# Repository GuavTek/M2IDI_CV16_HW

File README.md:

This eurorack module has 16 general purpose outputs which can be used for: CV, gates, envelopes, LFOs+++. 
View this project on [CADLAB.io](https://cadlab.io/project/25235) to see renders of schematics and PCBs, as well as current issues. 

<h2> A part of the M2IDI prototypes </h2>

<p>
The code for this module can be found on  
<a href="https://github.com/GuavTek/M2IDI_CV16">
			  GitHub
		  </a>
</p>

<p> 
More info on the M2IDI system can be found on the 
<a href="https://hackaday.io/project/182092-modular-midi">
			  Hackaday project page
		  </a>

</p>

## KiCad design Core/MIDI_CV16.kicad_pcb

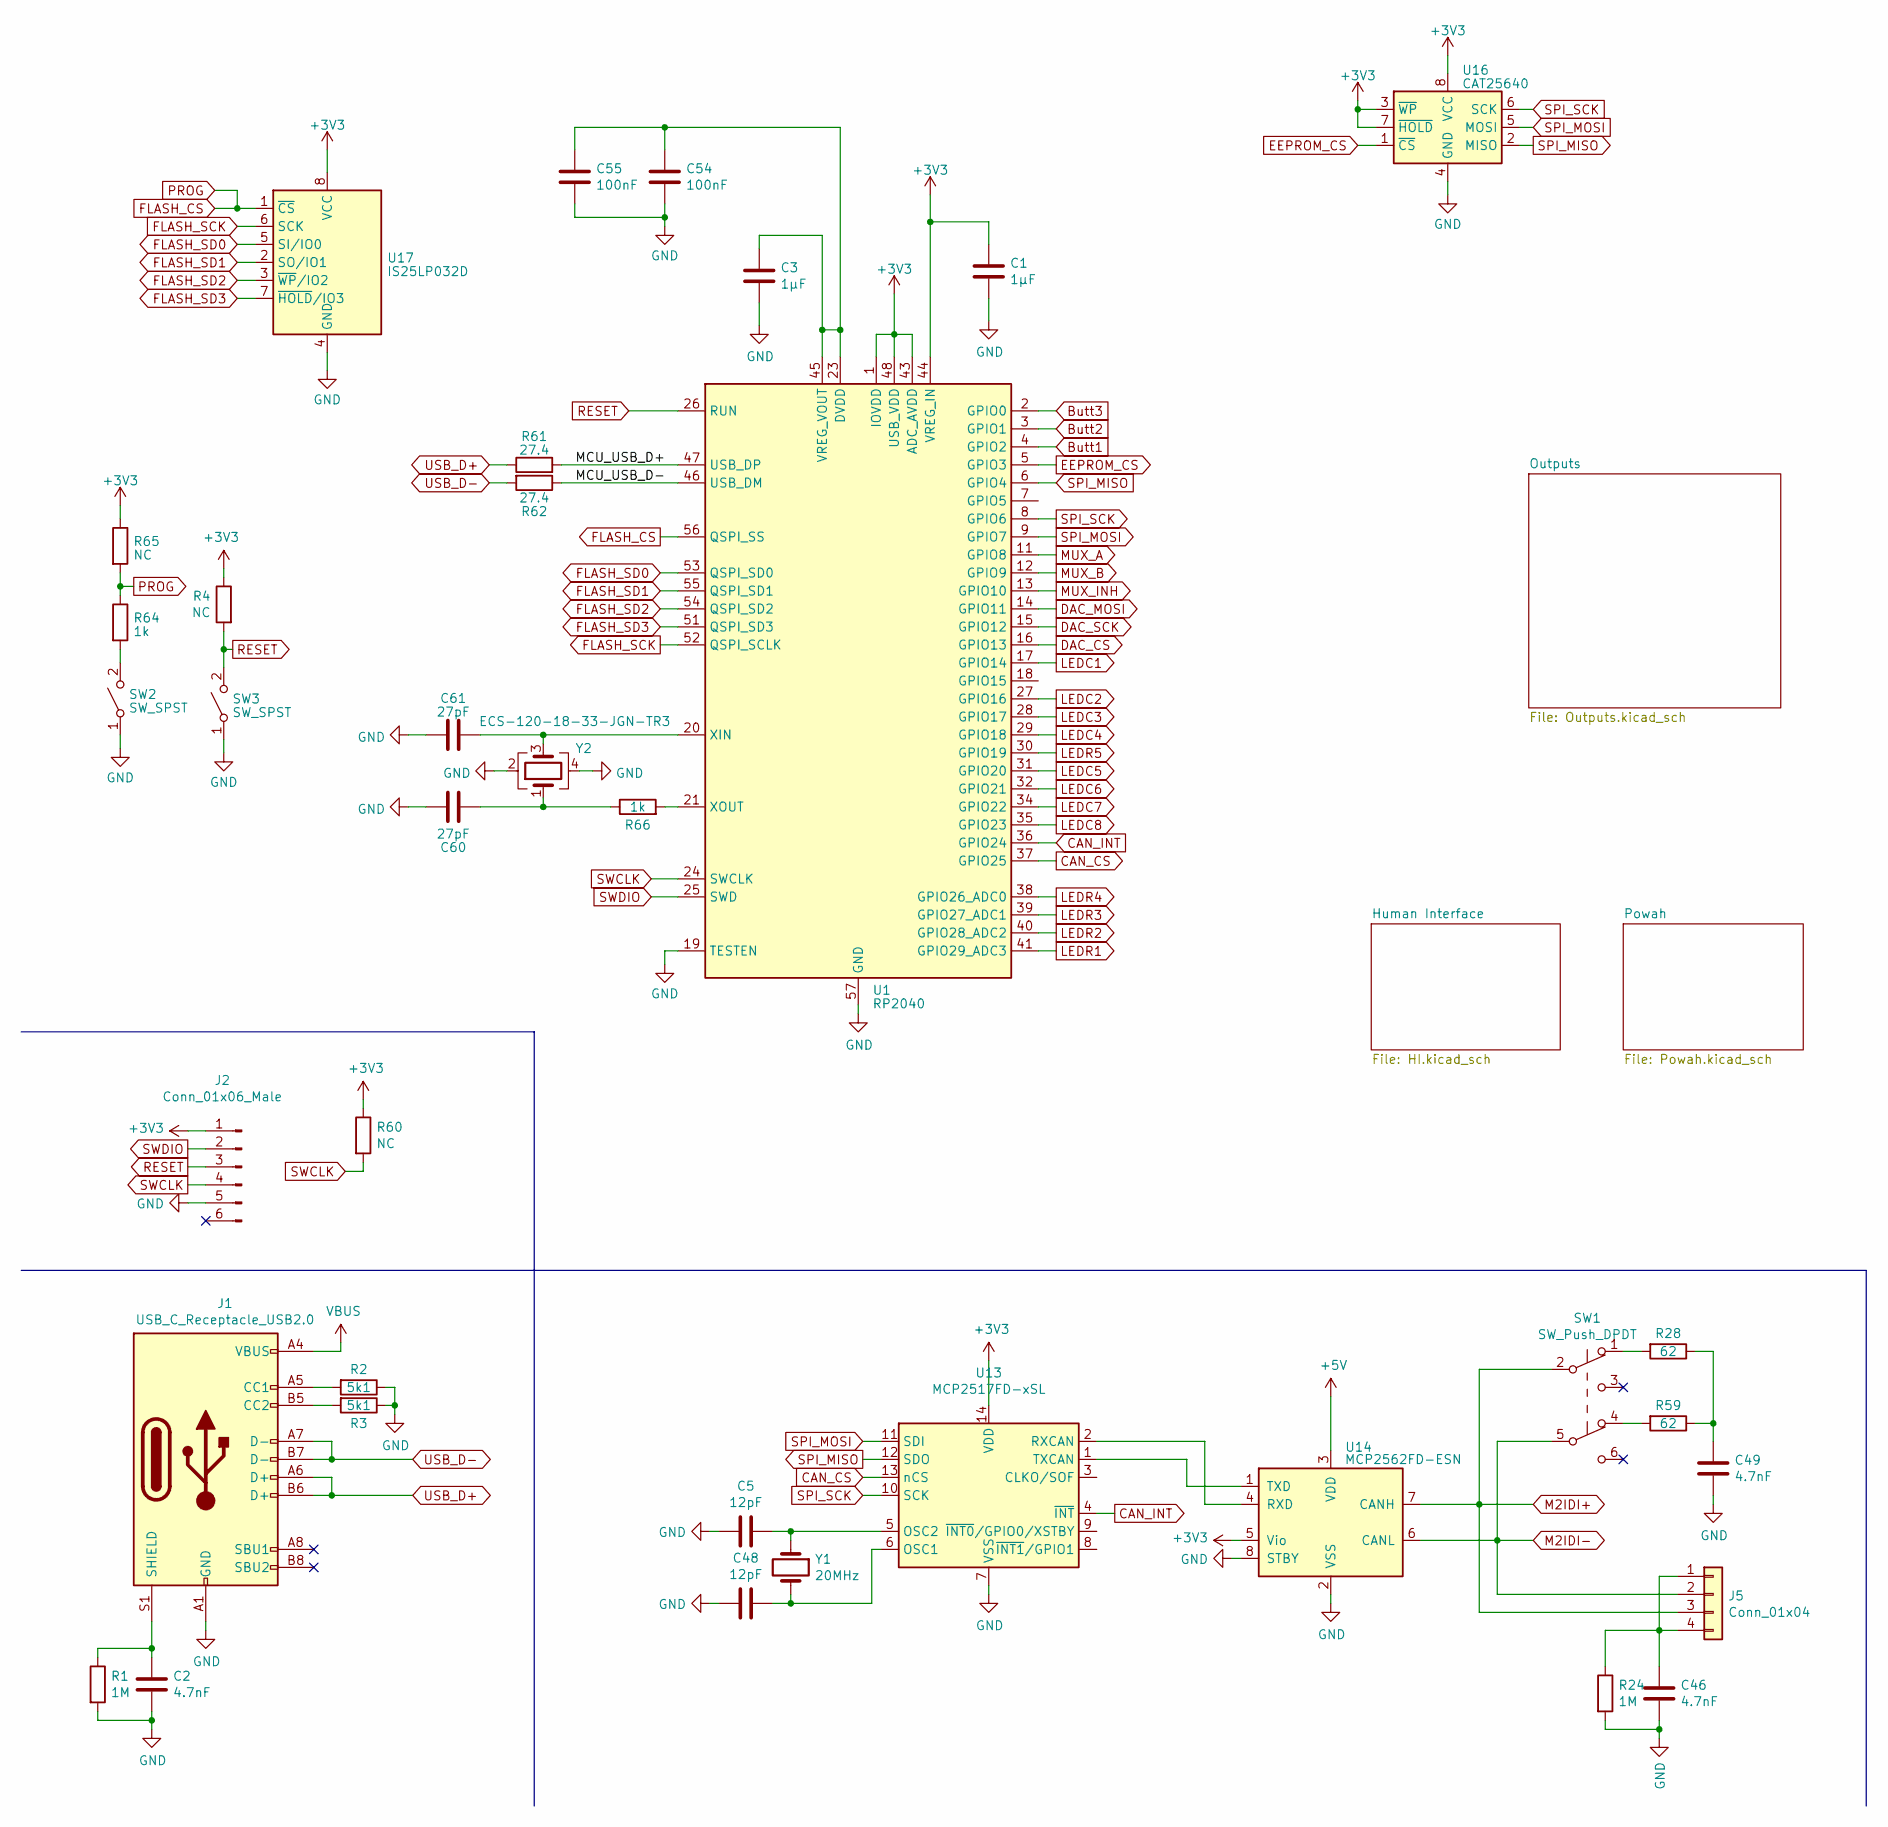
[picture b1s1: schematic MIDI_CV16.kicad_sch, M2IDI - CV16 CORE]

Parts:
C1, C3: 1µF; C_0603_1608Metric
C2, C46, C49: 4.7nF; C_0603_1608Metric
C5, C48: 12pF; C_0603_1608Metric
C54, C55: 100nF; C_0603_1608Metric
C60, C61: 27pF; C_0603_1608Metric
J1: USB_C_Receptacle_USB2.0; USB_C_Receptacle_HRO_TYPE-C-31-M-12
J2: Conn_01x06_Male; TSM103-DH
J5: Conn_01x04; MicroMatch_04_Vertical_SMD_Lock
R1, R24: 1M; R_0603_1608Metric
R2, R3: 5k1; R_0603_1608Metric
R4, R60, R65: NC; R_0603_1608Metric
R28, R59: 62; R_0805_2012Metric
R61, R62: 27.4; R_0603_1608Metric
R64, R66: 1k; R_0603_1608Metric
SW1: SW_Push_DPDT; SlideDPDT_JS202011
SW2, SW3: SW_SPST; Tactile_angled_SPST_5x5.4_SMD
U1: RP2040; QFN-56-1EP_7x7mm_P0.4mm_EP3.2x3.2mm
U13: MCP2517FD-xSL; SOIC-14_3.9x8.7mm_P1.27mm
U14: MCP2562FD-ESN; SOIC-8_3.9x4.9mm_P1.27mm
U16: CAT25640; SO-8_3.9x4.9mm_P1.27mm
U17: IS25LP032D; SOIC-8_3.9x4.9mm_P1.27mm
Y1: 20MHz; Crystal_2pin_2.0x2.5mm
Y2: ECS-120-18-33-JGN-TR3; Crystal_SMD_3225-4Pin_3.2x2.5mm_HandSoldering

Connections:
+3V3: C1.1, J2.1, R4.1, R60.1, R65.1, U1.1 (IOVDD), U1.10 (IOVDD), U1.22 (IOVDD), U1.33 (IOVDD), U1.42 (IOVDD), U1.43 (ADC_AVDD), U1.44 (VREG_IN), U1.48 (USB_VDD), U1.49 (IOVDD), U13.14 (VDD), U14.5 (Vio), U16.3 (~WP), U16.7 (~HOLD), U16.8 (VCC), U17.8 (VCC); also elsewhere on the board
+5V: U14.3 (VDD); also elsewhere on the board
/MCU_USB_D+: R61.2, U1.47 (USB_DP)
/MCU_USB_D-: R62.1, U1.46 (USB_DM)
Butt1: U1.4 (GPIO2); also elsewhere on the board
Butt2: U1.3 (GPIO1); also elsewhere on the board
Butt3: U1.2 (GPIO0); also elsewhere on the board
CAN_CS: U1.37 (GPIO25), U13.13 (nCS)
CAN_INT: U1.36 (GPIO24), U13.4 (~INT)
DAC_CS: U1.16 (GPIO13); also elsewhere on the board
DAC_MOSI: U1.14 (GPIO11); also elsewhere on the board
DAC_SCK: U1.15 (GPIO12); also elsewhere on the board
EEPROM_CS: U1.5 (GPIO3), U16.1 (~CS)
FLASH_CS: R64.1, R65.2, U1.56 (QSPI_SS), U17.1 (~CS)
FLASH_SCK: U1.52 (QSPI_SCLK), U17.6 (SCK)
FLASH_SD0: U1.53 (QSPI_SD0), U17.5 (SI/IO0)
FLASH_SD1: U1.55 (QSPI_SD1), U17.2 (SO/IO1)
FLASH_SD2: U1.54 (QSPI_SD2), U17.3 (~WP/IO2)
FLASH_SD3: U1.51 (QSPI_SD3), U17.7 (~HOLD/IO3)
GND: C1.2, C2.2, C3.2, C5.2, C46.2, C48.2, C49.2, C54.2, C55.2, C60.1, C61.1, J1.A1 (GND), J1.A12 (GND), J1.B1 (GND), J1.B12 (GND), J2.5, R1.2, R2.1, R3.1, R24.2, SW2.1 (A), SW3.1 (A), U1.19 (TESTEN), U1.57 (GND), U13.7 (VSS), U14.2 (VSS), U14.8 (STBY), U16.4 (GND), U17.4 (GND), Y2.2, Y2.4; also elsewhere on the board
LEDC1: U1.17 (GPIO14); also elsewhere on the board
LEDC2: U1.27 (GPIO16); also elsewhere on the board
LEDC3: U1.28 (GPIO17); also elsewhere on the board
LEDC4: U1.29 (GPIO18); also elsewhere on the board
LEDC5: U1.31 (GPIO20); also elsewhere on the board
LEDC6: U1.32 (GPIO21); also elsewhere on the board
LEDC7: U1.34 (GPIO22); also elsewhere on the board
LEDC8: U1.35 (GPIO23); also elsewhere on the board
LEDR1: U1.41 (GPIO29_ADC3); also elsewhere on the board
LEDR2: U1.40 (GPIO28_ADC2); also elsewhere on the board
LEDR3: U1.39 (GPIO27_ADC1); also elsewhere on the board
LEDR4: U1.38 (GPIO26_ADC0); also elsewhere on the board
LEDR5: U1.30 (GPIO19); also elsewhere on the board
M2IDI+: J5.3, SW1.2 (B), U14.7 (CANH)
M2IDI-: J5.2, SW1.5 (B), U14.6 (CANL)
MUX_A: U1.11 (GPIO8); also elsewhere on the board
MUX_B: U1.12 (GPIO9); also elsewhere on the board
MUX_INH: U1.13 (GPIO10); also elsewhere on the board
unnamed: C49.1, R28.1, R59.1
unnamed: C60.2, R66.1, Y2.1
unnamed: J1.A5 (CC1), R2.2
unnamed: J1.B5 (CC2), R3.2
unnamed: C2.1, J1.S1 (SHIELD), R1.1
unnamed: C46.1, J5.1, J5.4, R24.1
unnamed: R28.2, SW1.1 (A)
unnamed: R59.2, SW1.4 (A)
unnamed: R64.2, SW2.2 (B)
unnamed: C3.1, C54.1, C55.1, U1.23 (DVDD), U1.45 (VREG_VOUT), U1.50 (DVDD)
unnamed: C61.2, U1.20 (XIN), Y2.3
unnamed: R66.2, U1.21 (XOUT)
unnamed: C48.1, U13.6 (OSC1), Y1.2
unnamed: C5.1, U13.5 (OSC2), Y1.1
unnamed: U13.2 (RXCAN), U14.4 (RXD)
unnamed: U13.1 (TXCAN), U14.1 (TXD)
RESET: J2.3, R4.2, SW3.2 (B), U1.26 (RUN)
SPI_MISO: U1.6 (GPIO4), U13.12 (SDO), U16.2 (MISO)
SPI_MOSI: U1.9 (GPIO7), U13.11 (SDI), U16.5 (MOSI)
SPI_SCK: U1.8 (GPIO6), U13.10 (SCK), U16.6 (SCK)
SWCLK: J2.4, R60.2, U1.24 (SWCLK)
SWDIO: J2.2, U1.25 (SWD)
USB_D+: J1.A6 (D+), J1.B6 (D+), R61.1
USB_D-: J1.A7 (D-), J1.B7 (D-), R62.2
VBUS: J1.A4 (VBUS), J1.A9 (VBUS), J1.B4 (VBUS), J1.B9 (VBUS); also elsewhere on the board

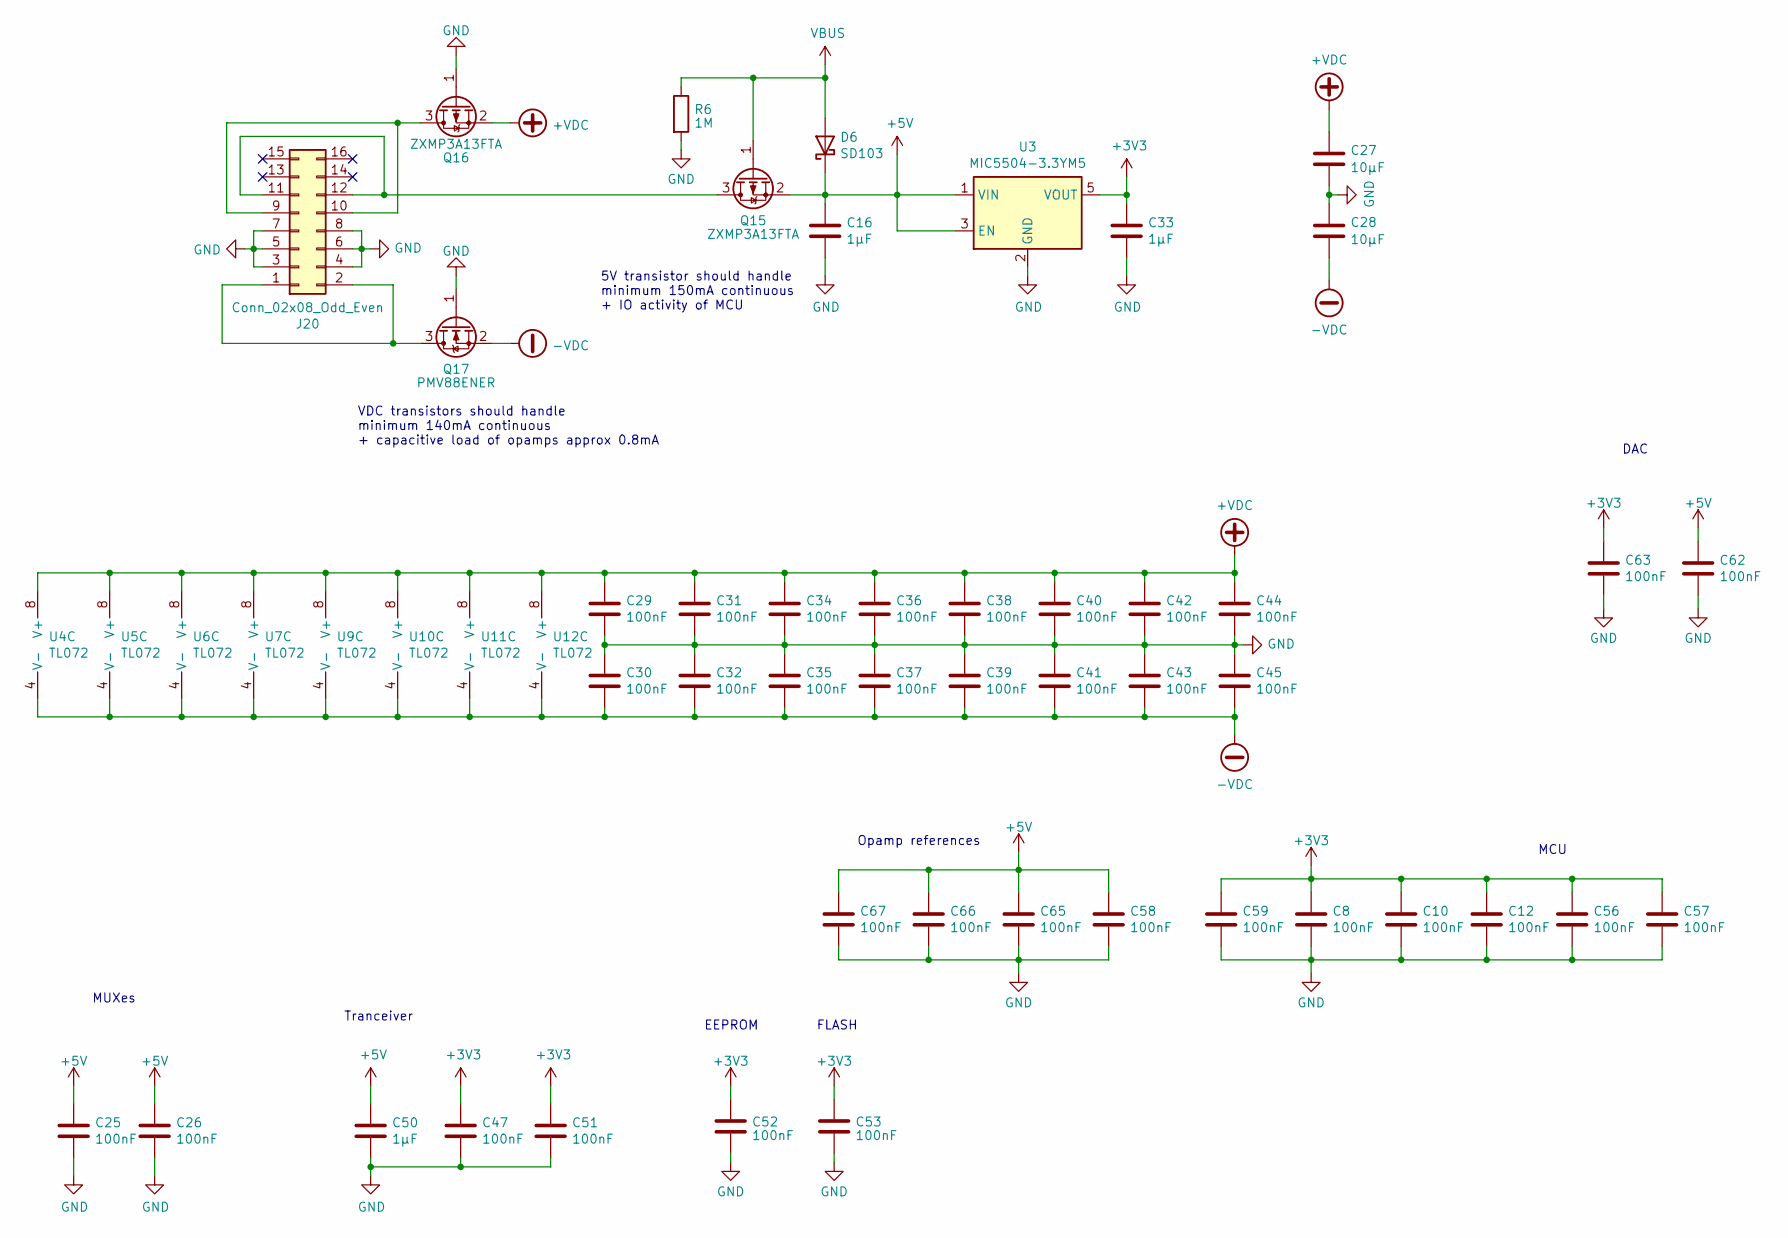
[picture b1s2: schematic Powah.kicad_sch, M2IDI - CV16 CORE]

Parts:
C8, C10, C12, C25, C26, C29, C30, C31, C32, C34, C35, C36, C37, C38, C39, C40, C41, C42, C43, C44, C45, C47, C51, C52, C53, C56, C57, C58, C59, C62, C63, C65, C66, C67: 100nF; C_0603_1608Metric
C16, C33, C50: 1µF; C_0603_1608Metric
C27, C28: 10µF; C_0805_2012Metric
D6: SD103; D_SOD-323_HandSoldering
J20: Conn_02x08_Odd_Even; Header_2x8_Shrouded_SMD
Q15, Q16: ZXMP3A13FTA; SOT-23
Q17: PMV88ENER; SOT-23
R6: 1M; R_0603_1608Metric
U3: MIC5504-3.3YM5; SOT-23-5
U4, U5, U6, U7, U9, U10, U11, U12: TL072; SOIC-8_3.9x4.9mm_P1.27mm

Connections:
+3V3: C8.1, C10.1, C12.1, C33.1, C47.1, C51.1, C52.1, C53.1, C56.1, C57.1, C59.1, C63.1, U3.5 (VOUT); also elsewhere on the board
+5V: C16.1, C25.1, C26.1, C50.1, C58.1, C62.1, C65.1, C66.1, C67.1, D6.1 (K), Q15.2 (S), U3.1 (VIN), U3.3 (EN); also elsewhere on the board
+VDC: C27.1, C29.1, C31.1, C34.1, C36.1, C38.1, C40.1, C42.1, C44.1, Q16.2 (S), U4.8 (V+), U5.8 (V+), U6.8 (V+), U7.8 (V+), U9.8 (V+), U10.8 (V+), U11.8 (V+), U12.8 (V+); also elsewhere on the board
-VDC: C28.2, C30.2, C32.2, C35.2, C37.2, C39.2, C41.2, C43.2, C45.2, Q17.2 (S), U4.4 (V-), U5.4 (V-), U6.4 (V-), U7.4 (V-), U9.4 (V-), U10.4 (V-), U11.4 (V-), U12.4 (V-); also elsewhere on the board
GND: C8.2, C10.2, C12.2, C16.2, C25.2, C26.2, C27.2, C28.1, C29.2, C30.1, C31.2, C32.1, C33.2, C34.2, C35.1, C36.2, C37.1, C38.2, C39.1, C40.2, C41.1, C42.2, C43.1, C44.2, C45.1, C47.2, C50.2, C51.2, C52.2, C53.2, C56.2, C57.2, C58.2, C59.2, C62.2, C63.2, C65.2, C66.2, C67.2, J20.3, J20.4, J20.5, J20.6, J20.7, J20.8, Q16.1 (G), Q17.1 (G), R6.2, U3.2 (GND); also elsewhere on the board
unnamed: J20.1, J20.2, Q17.3 (D)
unnamed: J20.9, J20.10, Q16.3 (D)
unnamed: J20.11, J20.12, Q15.3 (D)
VBUS: D6.2 (A), Q15.1 (G), R6.1; also elsewhere on the board

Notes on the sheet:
Opamp references
MUXes
EEPROM
DAC
VDC transistors should handle minimum 140mA continuous + capacitive load of opamps approx 0.8mA
Tranceiver
MCU
5V transistor should handle minimum 150mA continuous + IO activity of MCU
FLASH

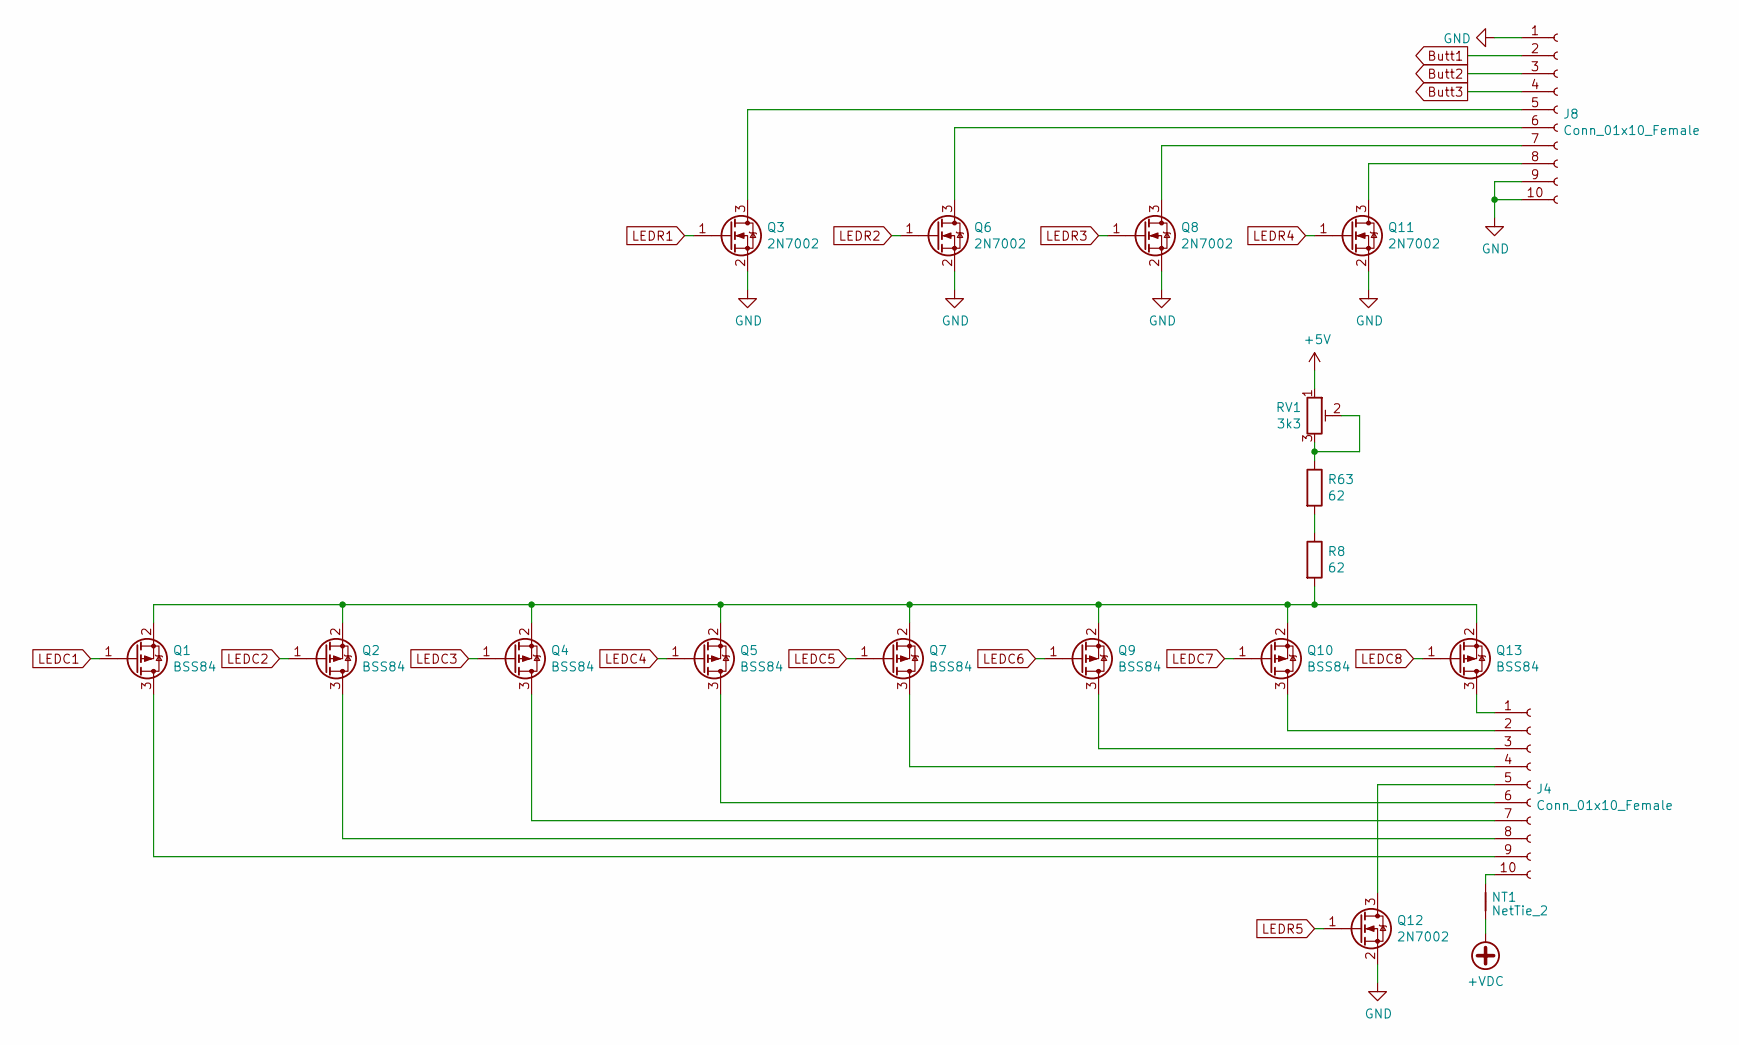
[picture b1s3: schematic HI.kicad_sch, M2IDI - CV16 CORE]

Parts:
J4, J8: Conn_01x10_Female; PinSocket_1x10_P2.54mm_Vertical_SMD_Pin1Both
NT1: NetTie_2; NetTie_NC0603
Q1, Q2, Q4, Q5, Q7, Q9, Q10, Q13: BSS84; SOT-23
Q3, Q6, Q8, Q11, Q12: 2N7002; SOT-23
R8, R63: 62; R_0805_2012Metric
RV1: 3k3; VG039N

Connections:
+5V: RV1.1; also elsewhere on the board
+VDC: NT1.1; also elsewhere on the board
Butt1: J8.2; also elsewhere on the board
Butt2: J8.3; also elsewhere on the board
Butt3: J8.4; also elsewhere on the board
GND: J8.1, J8.9, J8.10, Q3.2 (S), Q6.2 (S), Q8.2 (S), Q11.2 (S), Q12.2 (S); also elsewhere on the board
LEDC1: Q1.1 (G); also elsewhere on the board
LEDC2: Q2.1 (G); also elsewhere on the board
LEDC3: Q4.1 (G); also elsewhere on the board
LEDC4: Q5.1 (G); also elsewhere on the board
LEDC5: Q7.1 (G); also elsewhere on the board
LEDC6: Q9.1 (G); also elsewhere on the board
LEDC7: Q10.1 (G); also elsewhere on the board
LEDC8: Q13.1 (G); also elsewhere on the board
LEDR1: Q3.1 (G); also elsewhere on the board
LEDR2: Q6.1 (G); also elsewhere on the board
LEDR3: Q8.1 (G); also elsewhere on the board
LEDR4: Q11.1 (G); also elsewhere on the board
LEDR5: Q12.1 (G); also elsewhere on the board
unnamed: J4.1, Q13.3 (D)
unnamed: J4.2, Q10.3 (D)
unnamed: J4.3, Q9.3 (D)
unnamed: J4.4, Q7.3 (D)
unnamed: J4.5, Q12.3 (D)
unnamed: J4.6, Q5.3 (D)
unnamed: J4.7, Q4.3 (D)
unnamed: J4.8, Q2.3 (D)
unnamed: J4.9, Q1.3 (D)
unnamed: J4.10, NT1.2
unnamed: J8.5, Q3.3 (D)
unnamed: J8.6, Q6.3 (D)
unnamed: J8.7, Q8.3 (D)
unnamed: J8.8, Q11.3 (D)
unnamed: Q1.2 (S), Q2.2 (S), Q4.2 (S), Q5.2 (S), Q7.2 (S), Q9.2 (S), Q10.2 (S), Q13.2 (S), R8.2
unnamed: R63.1, RV1.2, RV1.3
unnamed: R8.1, R63.2

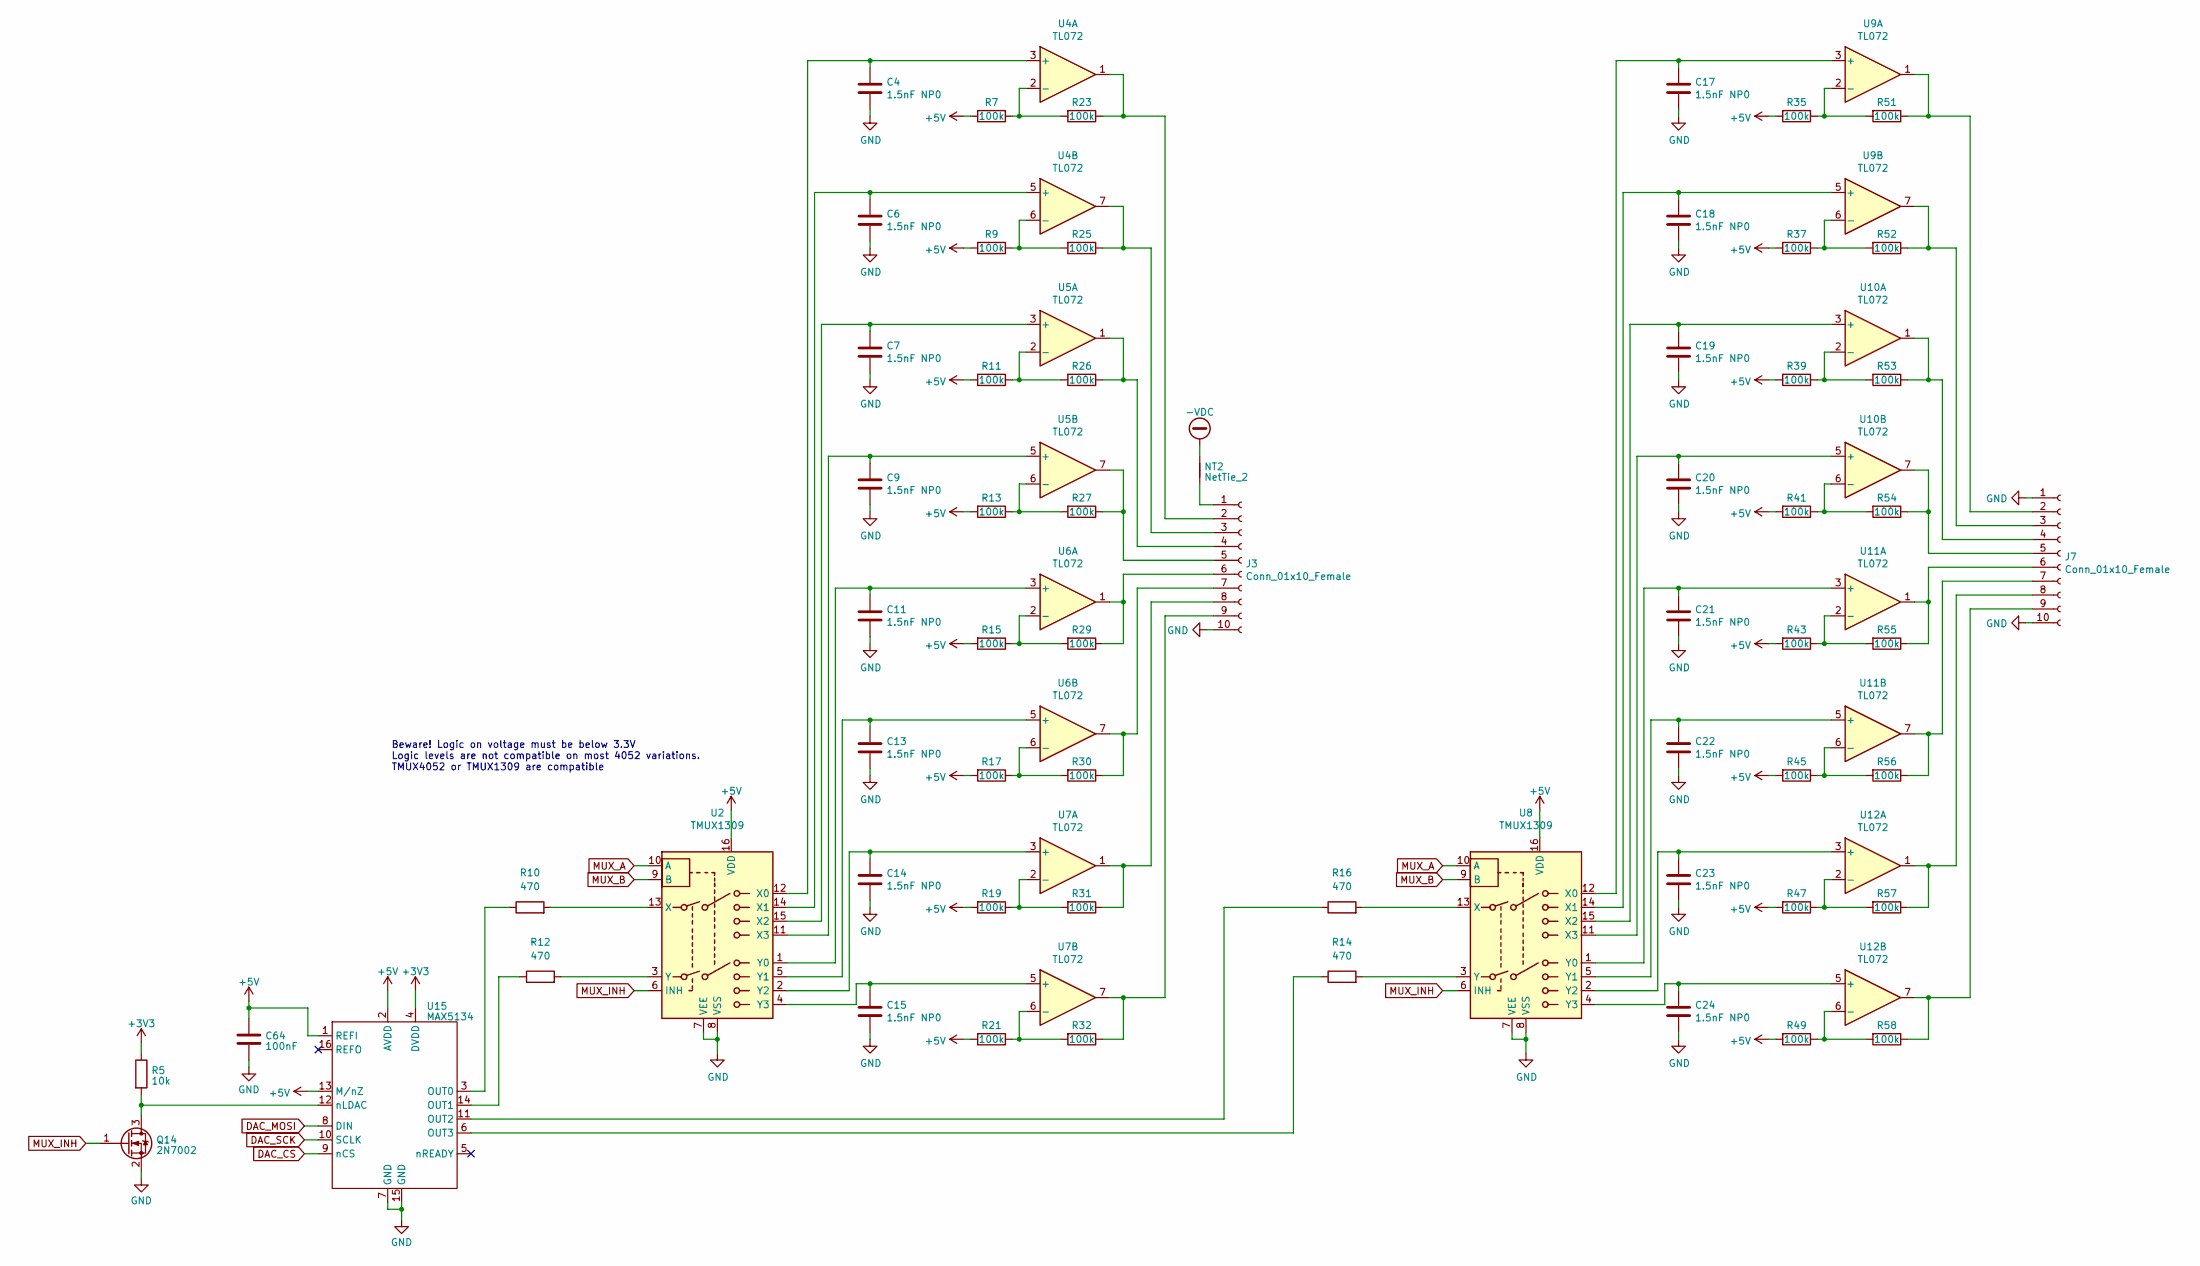
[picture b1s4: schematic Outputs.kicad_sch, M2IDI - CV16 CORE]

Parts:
C4, C6, C7, C9, C11, C13, C14, C15, C17, C18, C19, C20, C21, C22, C23, C24: 1.5nF NP0; C_0603_1608Metric
C64: 100nF; C_0603_1608Metric
J3, J7: Conn_01x10_Female; PinSocket_1x10_P2.54mm_Vertical_SMD_Pin1Both
NT2: NetTie_2; NetTie_NC0603
Q14: 2N7002; SOT-23
R5: 10k; R_0603_1608Metric
R7, R9, R11, R13, R15, R17, R19, R21, R23, R25, R26, R27, R29, R30, R31, R32, R35, R37, R39, R41, R43, R45, R47, R49, R51, R52, R53, R54, R55, R56, R57, R58: 100k; R_0603_1608Metric
R10, R12, R14, R16: 470; R_0603_1608Metric
U2, U8: TMUX1309; TSSOP-16_4.4x5mm_P0.65mm
U4, U5, U6, U7, U9, U10, U11, U12: TL072; SOIC-8_3.9x4.9mm_P1.27mm
U15: MAX5134; TSSOP-16_4.4x5mm_P0.65mm

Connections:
+3V3: R5.1, U15.4 (DVDD); also elsewhere on the board
+5V: C64.1, R7.2, R9.2, R11.2, R13.2, R15.2, R17.2, R19.2, R21.2, R35.2, R37.2, R39.2, R41.2, R43.2, R45.2, R47.2, R49.2, U2.16 (VDD), U8.16 (VDD), U15.1 (REFI), U15.2 (AVDD), U15.13 (M/nZ); also elsewhere on the board
-VDC: NT2.2; also elsewhere on the board
DAC_CS: U15.9 (nCS); also elsewhere on the board
DAC_MOSI: U15.8 (DIN); also elsewhere on the board
DAC_SCK: U15.10 (SCLK); also elsewhere on the board
GND: C4.2, C6.2, C7.2, C9.2, C11.2, C13.2, C14.2, C15.2, C17.2, C18.2, C19.2, C20.2, C21.2, C22.2, C23.2, C24.2, C64.2, J3.10, J7.1, J7.10, Q14.2 (S), U2.7 (VEE), U2.8 (VSS), U8.7 (VEE), U8.8 (VSS), U15.7 (GND), U15.15 (GND); also elsewhere on the board
MUX_A: U2.10 (A), U8.10 (A); also elsewhere on the board
MUX_B: U2.9 (B), U8.9 (B); also elsewhere on the board
MUX_INH: Q14.1 (G), U2.6 (INH), U8.6 (INH); also elsewhere on the board
unnamed: J3.1, NT2.1
unnamed: J3.2, R23.1, U4.1
unnamed: J3.3, R25.1, U4.7
unnamed: J3.4, R26.1, U5.1
unnamed: J3.5, R27.1, U5.7
unnamed: J3.6, R29.1, U6.1
unnamed: J3.7, R30.1, U6.7
unnamed: J3.8, R31.1, U7.1
unnamed: J3.9, R32.1, U7.7
unnamed: J7.2, R51.1, U9.1
unnamed: J7.3, R52.1, U9.7
unnamed: J7.4, R53.1, U10.1
unnamed: J7.5, R54.1, U10.7
unnamed: J7.6, R55.1, U11.1
unnamed: J7.7, R56.1, U11.7
unnamed: J7.8, R57.1, U12.1
unnamed: J7.9, R58.1, U12.7
unnamed: Q14.3 (D), R5.2, U15.12 (nLDAC)
unnamed: C4.1, U2.12 (X0), U4.3 (+)
unnamed: C6.1, U2.14 (X1), U4.5 (+)
unnamed: C7.1, U2.15 (X2), U5.3 (+)
unnamed: C9.1, U2.11 (X3), U5.5 (+)
unnamed: R10.2, U2.13 (X)
unnamed: C11.1, U2.1 (Y0), U6.3 (+)
unnamed: C13.1, U2.5 (Y1), U6.5 (+)
unnamed: C14.1, U2.2 (Y2), U7.3 (+)
unnamed: C15.1, U2.4 (Y3), U7.5 (+)
unnamed: R12.2, U2.3 (Y)
unnamed: R7.1, R23.2, U4.2 (-)
unnamed: R9.1, R25.2, U4.6 (-)
unnamed: R11.1, R26.2, U5.2 (-)
unnamed: R13.1, R27.2, U5.6 (-)
unnamed: R15.1, R29.2, U6.2 (-)
unnamed: R17.1, R30.2, U6.6 (-)
unnamed: R19.1, R31.2, U7.2 (-)
unnamed: R21.1, R32.2, U7.6 (-)
unnamed: C17.1, U8.12 (X0), U9.3 (+)
unnamed: C18.1, U8.14 (X1), U9.5 (+)
unnamed: R16.2, U8.13 (X)
unnamed: R14.2, U8.3 (Y)
unnamed: R35.1, R51.2, U9.2 (-)
unnamed: R37.1, R52.2, U9.6 (-)
unnamed: C19.1, U8.15 (X2), U10.3 (+)
unnamed: R39.1, R53.2, U10.2 (-)
unnamed: C20.1, U8.11 (X3), U10.5 (+)
unnamed: R41.1, R54.2, U10.6 (-)
unnamed: C21.1, U8.1 (Y0), U11.3 (+)
unnamed: R43.1, R55.2, U11.2 (-)
unnamed: C22.1, U8.5 (Y1), U11.5 (+)
unnamed: R45.1, R56.2, U11.6 (-)
unnamed: C23.1, U8.2 (Y2), U12.3 (+)
unnamed: R47.1, R57.2, U12.2 (-)
unnamed: C24.1, U8.4 (Y3), U12.5 (+)
unnamed: R49.1, R58.2, U12.6 (-)
unnamed: R10.1, U15.3 (OUT0)
unnamed: R12.1, U15.14 (OUT1)
unnamed: R16.1, U15.11 (OUT2)
unnamed: R14.1, U15.6 (OUT3)

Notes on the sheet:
Beware! Logic on voltage must be below 3.3V Logic levels are not compatible on most 4052 variations. TMUX4052 or TMUX1309 are compatible

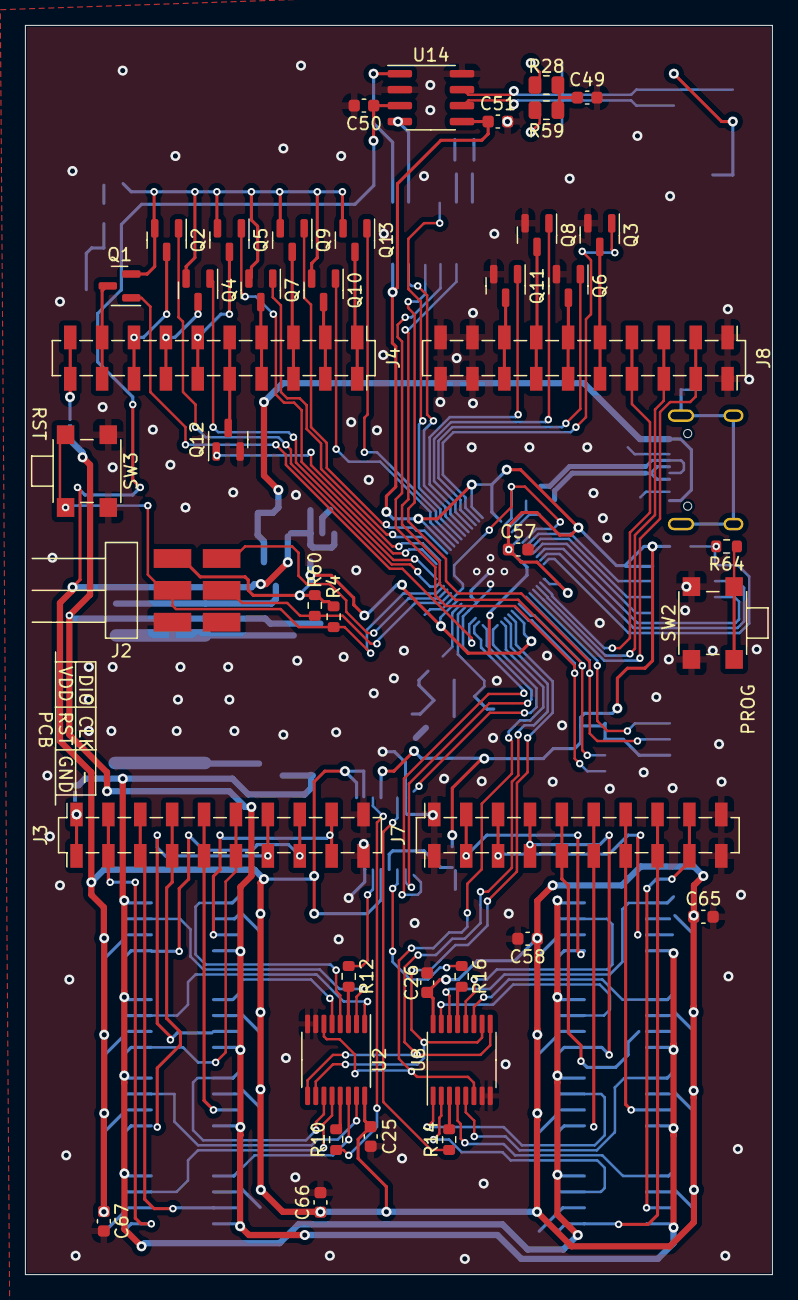
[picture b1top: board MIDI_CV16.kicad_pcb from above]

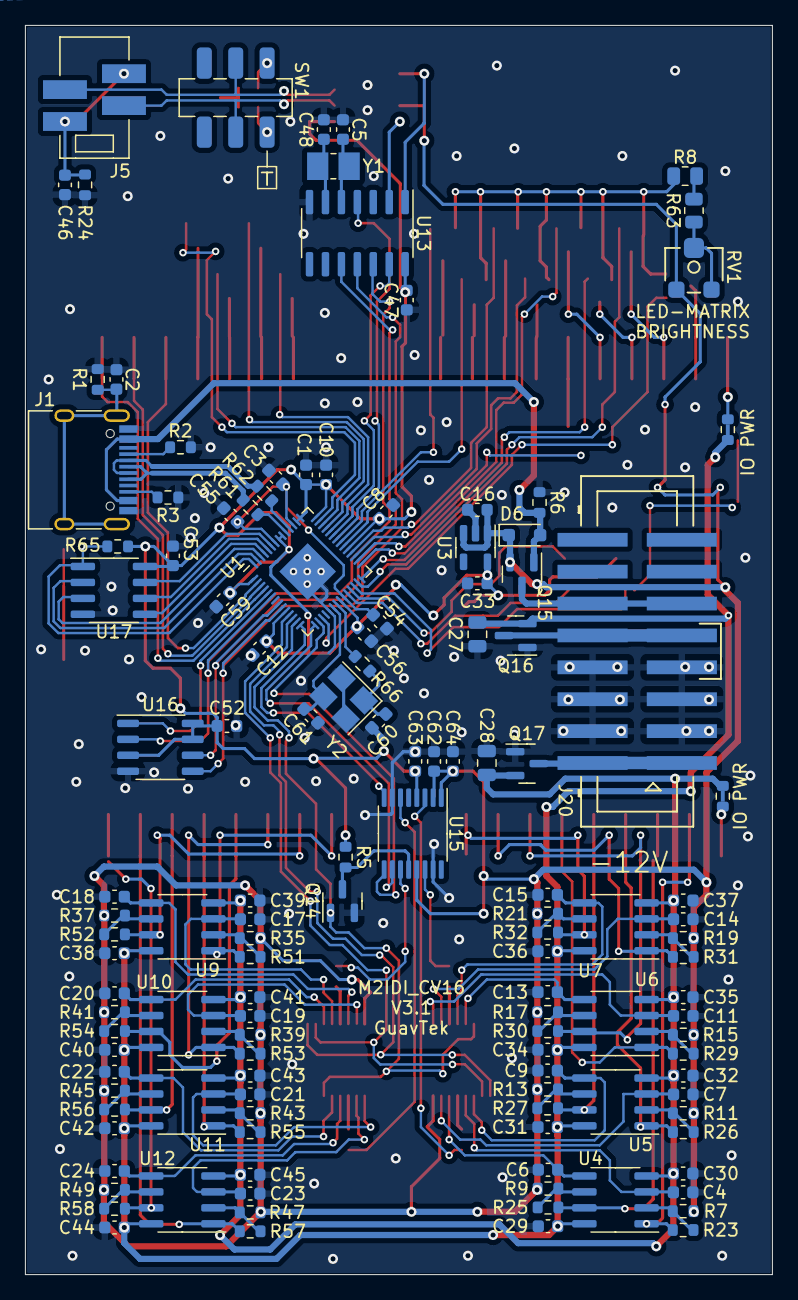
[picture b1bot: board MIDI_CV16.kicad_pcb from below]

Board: 2 copper layers, 59.5 x 99.5 mm, 171 parts (129 on the bottom side), 143 nets.

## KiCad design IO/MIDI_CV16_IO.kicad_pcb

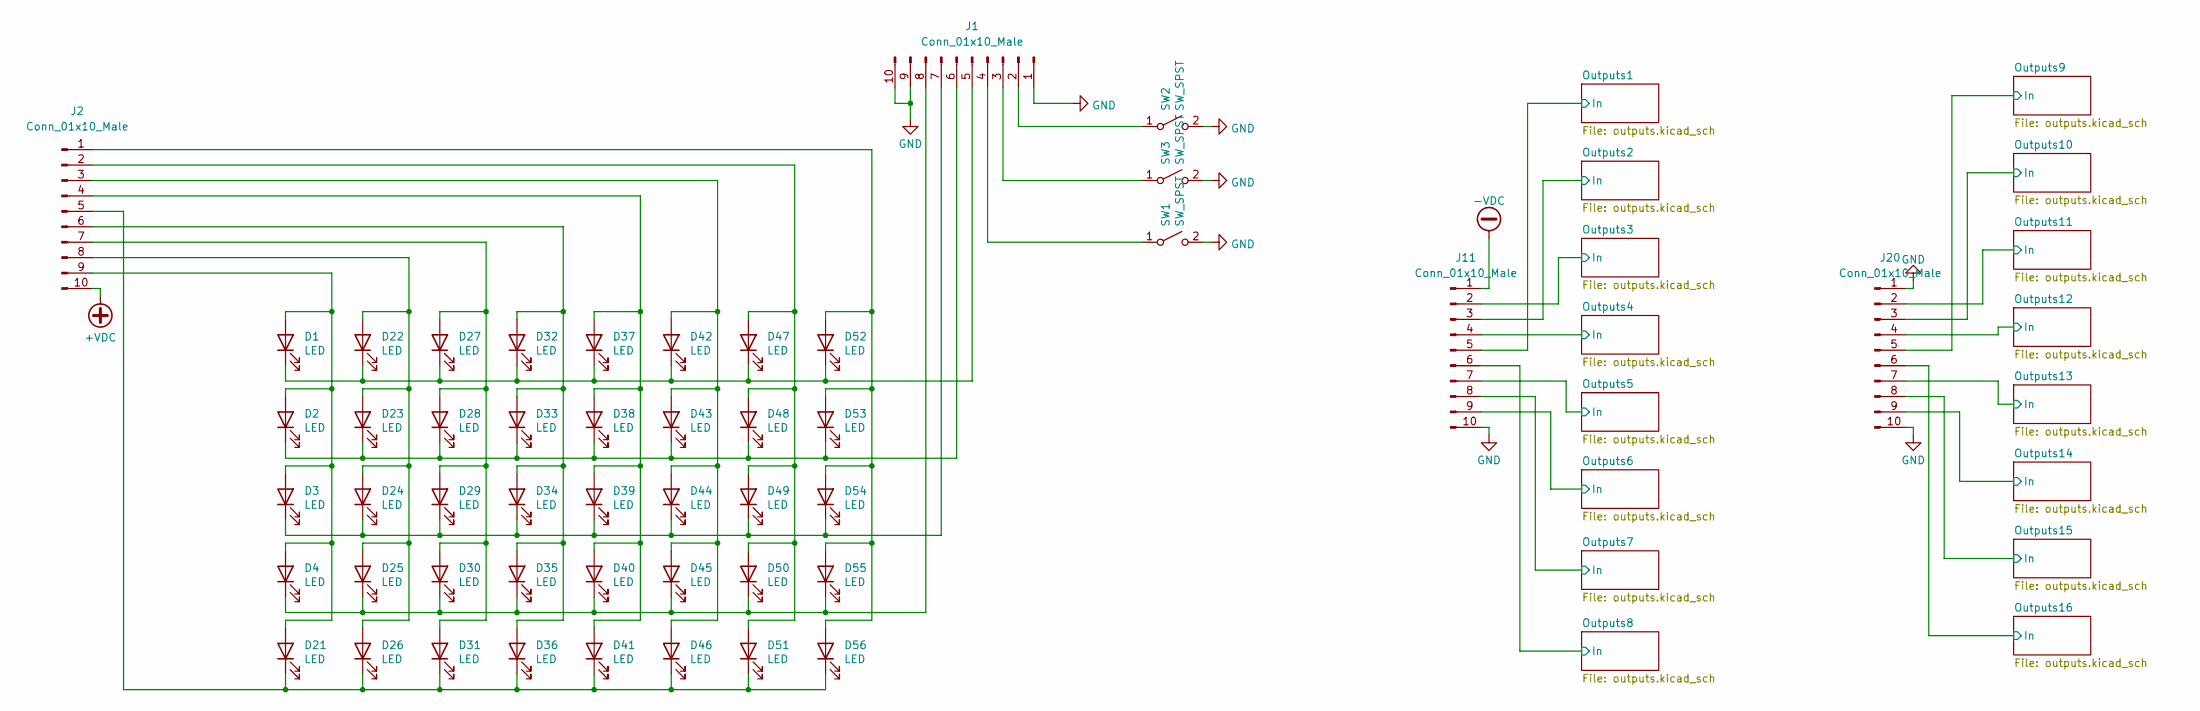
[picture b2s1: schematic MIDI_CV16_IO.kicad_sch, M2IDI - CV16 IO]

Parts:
D1, D2, D3, D4, D21, D22, D23, D24, D25, D26, D27, D28, D29, D30, D31, D32, D33, D34, D35, D36, D37, D38, D39, D40, D41, D42, D43, D44, D45, D46, D47, D48, D49, D50, D51, D52, D53, D54, D55, D56: LED; LED_D3.0mm_NoCourtyard
J1, J2, J11, J20: Conn_01x10_Male; PinHeader_1x10_P2.54mm_Vertical_SMD_Pin1Right
SW1, SW2, SW3: SW_SPST; SW_PUSH_6mm_H13mm

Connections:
+VDC: J2.10; also elsewhere on the board
-VDC: J11.1; also elsewhere on the board
/Outputs1/In: J11.5; also elsewhere on the board
/Outputs2/In: J11.3; also elsewhere on the board
/Outputs3/In: J11.2; also elsewhere on the board
/Outputs4/In: J11.4; also elsewhere on the board
/Outputs5/In: J11.7; also elsewhere on the board
/Outputs6/In: J11.9; also elsewhere on the board
/Outputs7/In: J11.8; also elsewhere on the board
/Outputs8/In: J11.6; also elsewhere on the board
/Outputs9/In: J20.5; also elsewhere on the board
/Outputs10/In: J20.3; also elsewhere on the board
/Outputs11/In: J20.2; also elsewhere on the board
/Outputs12/In: J20.4; also elsewhere on the board
/Outputs13/In: J20.7; also elsewhere on the board
/Outputs14/In: J20.9; also elsewhere on the board
/Outputs15/In: J20.8; also elsewhere on the board
/Outputs16/In: J20.6; also elsewhere on the board
GND: J1.1, J1.9, J1.10, J11.10, J20.1, J20.10, SW1.2 (B), SW2.2 (B), SW3.2 (B); also elsewhere on the board
unnamed: D1.2 (A), D2.2 (A), D3.2 (A), D4.2 (A), D21.2 (A), J2.9
unnamed: D1.1 (K), D22.1 (K), D27.1 (K), D32.1 (K), D37.1 (K), D42.1 (K), D47.1 (K), D52.1 (K), J1.5
unnamed: D2.1 (K), D23.1 (K), D28.1 (K), D33.1 (K), D38.1 (K), D43.1 (K), D48.1 (K), D53.1 (K), J1.6
unnamed: D21.1 (K), D26.1 (K), D31.1 (K), D36.1 (K), D41.1 (K), D46.1 (K), D51.1 (K), D56.1 (K), J2.5
unnamed: D22.2 (A), D23.2 (A), D24.2 (A), D25.2 (A), D26.2 (A), J2.8
unnamed: D3.1 (K), D24.1 (K), D29.1 (K), D34.1 (K), D39.1 (K), D44.1 (K), D49.1 (K), D54.1 (K), J1.7
unnamed: D4.1 (K), D25.1 (K), D30.1 (K), D35.1 (K), D40.1 (K), D45.1 (K), D50.1 (K), D55.1 (K), J1.8
unnamed: D27.2 (A), D28.2 (A), D29.2 (A), D30.2 (A), D31.2 (A), J2.7
unnamed: D32.2 (A), D33.2 (A), D34.2 (A), D35.2 (A), D36.2 (A), J2.6
unnamed: D37.2 (A), D38.2 (A), D39.2 (A), D40.2 (A), D41.2 (A), J2.4
unnamed: D42.2 (A), D43.2 (A), D44.2 (A), D45.2 (A), D46.2 (A), J2.3
unnamed: D47.2 (A), D48.2 (A), D49.2 (A), D50.2 (A), D51.2 (A), J2.2
unnamed: D52.2 (A), D53.2 (A), D54.2 (A), D55.2 (A), D56.2 (A), J2.1
unnamed: J1.2, SW2.1 (A)
unnamed: J1.3, SW3.1 (A)
unnamed: J1.4, SW1.1 (A)
